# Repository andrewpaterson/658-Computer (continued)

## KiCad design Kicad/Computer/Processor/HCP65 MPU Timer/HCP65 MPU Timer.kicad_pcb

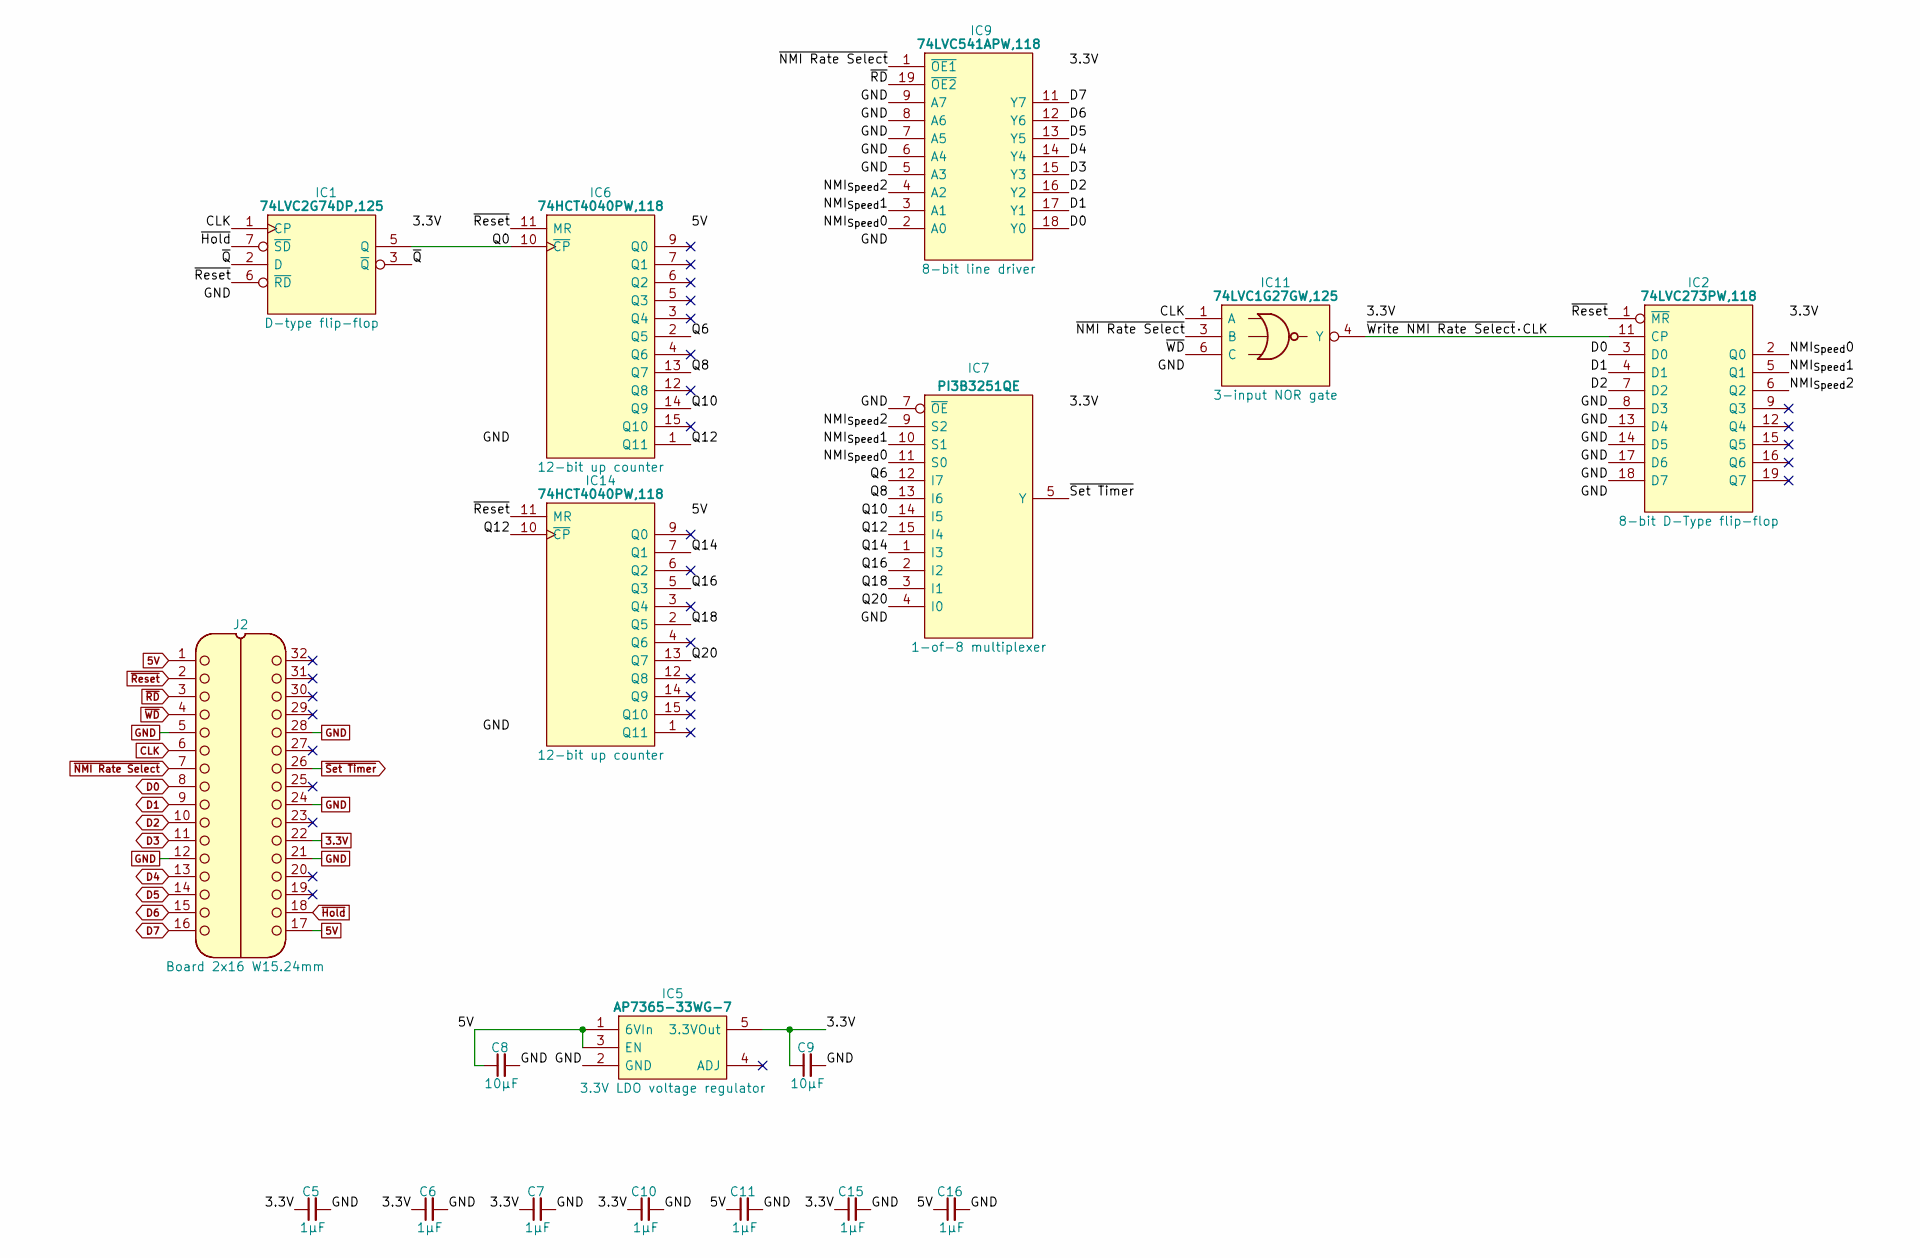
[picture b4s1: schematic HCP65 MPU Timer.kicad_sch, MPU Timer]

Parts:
C5, C6, C7, C10, C11, C15, C16: 1μF; C_0805
C8, C9: 10µF; C_0805
IC1: 74LVC2G74DP,125; SOP65P400X110-8N; Manufacturer_Part_Number 74LVC2G74DP,125; Mouser Part Number 771-74LVC2G74DP-G
IC2: 74LVC273PW,118; SOP65P640X110-20N; Manufacturer_Part_Number 74LVC273PW,118; Mouser Part Number 771-74LVC273PW-T
IC5: AP7365-33WG-7; SOT95P285X130-5N; Manufacturer_Part_Number AP7365-33WG-7; Mouser Part Number 621-AP7365-33WG-7
IC6, IC14: 74HCT4040PW,118; SOP65P640X110-16N; Manufacturer_Part_Number 74HCT4040PW,118; Mouser Part Number 771-HCT4040PW118
IC7: PI3B3251QE; SOP64P599X175-16N; Manufacturer_Part_Number PI3B3251QE; Mouser Part Number 729-PI3B3251QE
IC9: 74LVC541APW,118; SOP65P640X110-20N; Mouser Part Number 771-74LVC541APW-T
IC11: 74LVC1G27GW,125; SOP65P210X110-6N; Mouser Part Number 771-74LVC1G27GW125
J2: Board 2x16 W15.24mm; DIP-32_Board_W15.24mm

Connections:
3.3V: C5.1, C6.1, C7.1, C9.1, C10.1, C15.1, IC1.8 (3V), IC2.20 (3V), IC5.5 (3.3VOut), IC7.16 (3V), IC9.20 (3V), IC11.5 (3V), J2.22
5V: C8.1, C11.1, C16.1, IC5.1 (6VIn), IC5.3 (EN), IC6.16 (5V), IC14.16 (5V), J2.1, J2.17
/NMI_{Speed}0: IC2.2 (Q0), IC7.11 (S0), IC9.2 (A0)
/NMI_{Speed}1: IC2.5 (Q1), IC7.10 (S1), IC9.3 (A1)
/NMI_{Speed}2: IC2.6 (Q2), IC7.9 (S2), IC9.4 (A2)
/Q0: IC1.5 (Q), IC6.10 (~CP)
/Q6: IC6.2 (Q5), IC7.12 (I7)
/Q8: IC6.13 (Q7), IC7.13 (I6)
/Q10: IC6.14 (Q9), IC7.14 (I5)
/Q12: IC6.1 (Q11), IC7.15 (I4), IC14.10 (~CP)
/Q14: IC7.1 (I3), IC14.7 (Q1)
/Q16: IC7.2 (I2), IC14.5 (Q3)
/Q18: IC7.3 (I1), IC14.2 (Q5)
/Q20: IC7.4 (I0), IC14.13 (Q7)
/~Q: IC1.2 (D), IC1.3 (~Q)
/~Write NMI Rate Select·CLK: IC2.11 (CP), IC11.4 (Y)
CLK: IC1.1 (CP), IC11.1 (A), J2.6
D0: IC2.3 (D0), IC9.18 (Y0), J2.8
D1: IC2.4 (D1), IC9.17 (Y1), J2.9
D2: IC2.7 (D2), IC9.16 (Y2), J2.10
D3: IC9.15 (Y3), J2.11
D4: IC9.14 (Y4), J2.13
D5: IC9.13 (Y5), J2.14
D6: IC9.12 (Y6), J2.15
D7: IC9.11 (Y7), J2.16
GND: C5.2, C6.2, C7.2, C8.2, C9.2, C10.2, C11.2, C15.2, C16.2, IC1.4 (GND), IC2.8 (D3), IC2.10 (GND), IC2.13 (D4), IC2.14 (D5), IC2.17 (D6), IC2.18 (D7), IC5.2 (GND), IC6.8 (GND), IC7.7 (~OE), IC7.8 (GND), IC9.5 (A3), IC9.6 (A4), IC9.7 (A5), IC9.8 (A6), IC9.9 (A7), IC9.10 (GND), IC11.2 (GND), IC14.8 (GND), J2.5, J2.12, J2.21, J2.24, J2.28
~Hold: IC1.7 (~SD), J2.18
~NMI Rate Select: IC9.1 (~OE1), IC11.3 (B), J2.7
~RD: IC9.19 (~OE2), J2.3
~Reset: IC1.6 (~RD), IC2.1 (~MR), IC6.11 (MR), IC14.11 (MR), J2.2
~Set Timer: IC7.5 (Y), J2.26
~WD: IC11.6 (C), J2.4

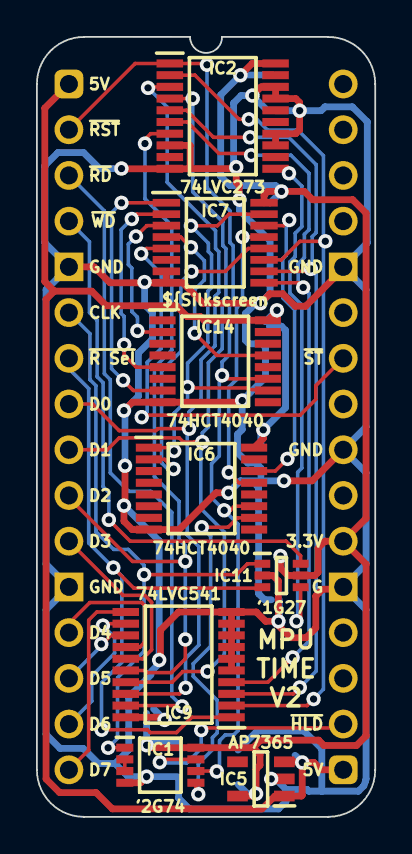
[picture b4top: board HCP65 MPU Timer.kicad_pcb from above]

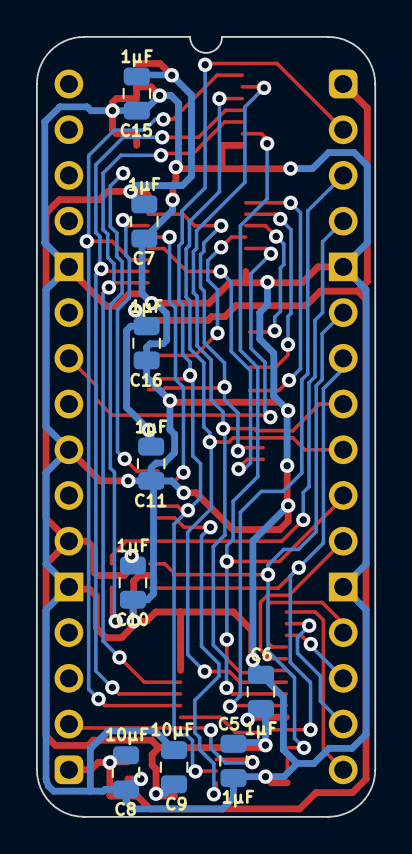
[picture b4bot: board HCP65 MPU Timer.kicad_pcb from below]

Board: 2 copper layers, 18.8 x 43.3 mm, 18 parts (9 on the bottom side), 32 nets.

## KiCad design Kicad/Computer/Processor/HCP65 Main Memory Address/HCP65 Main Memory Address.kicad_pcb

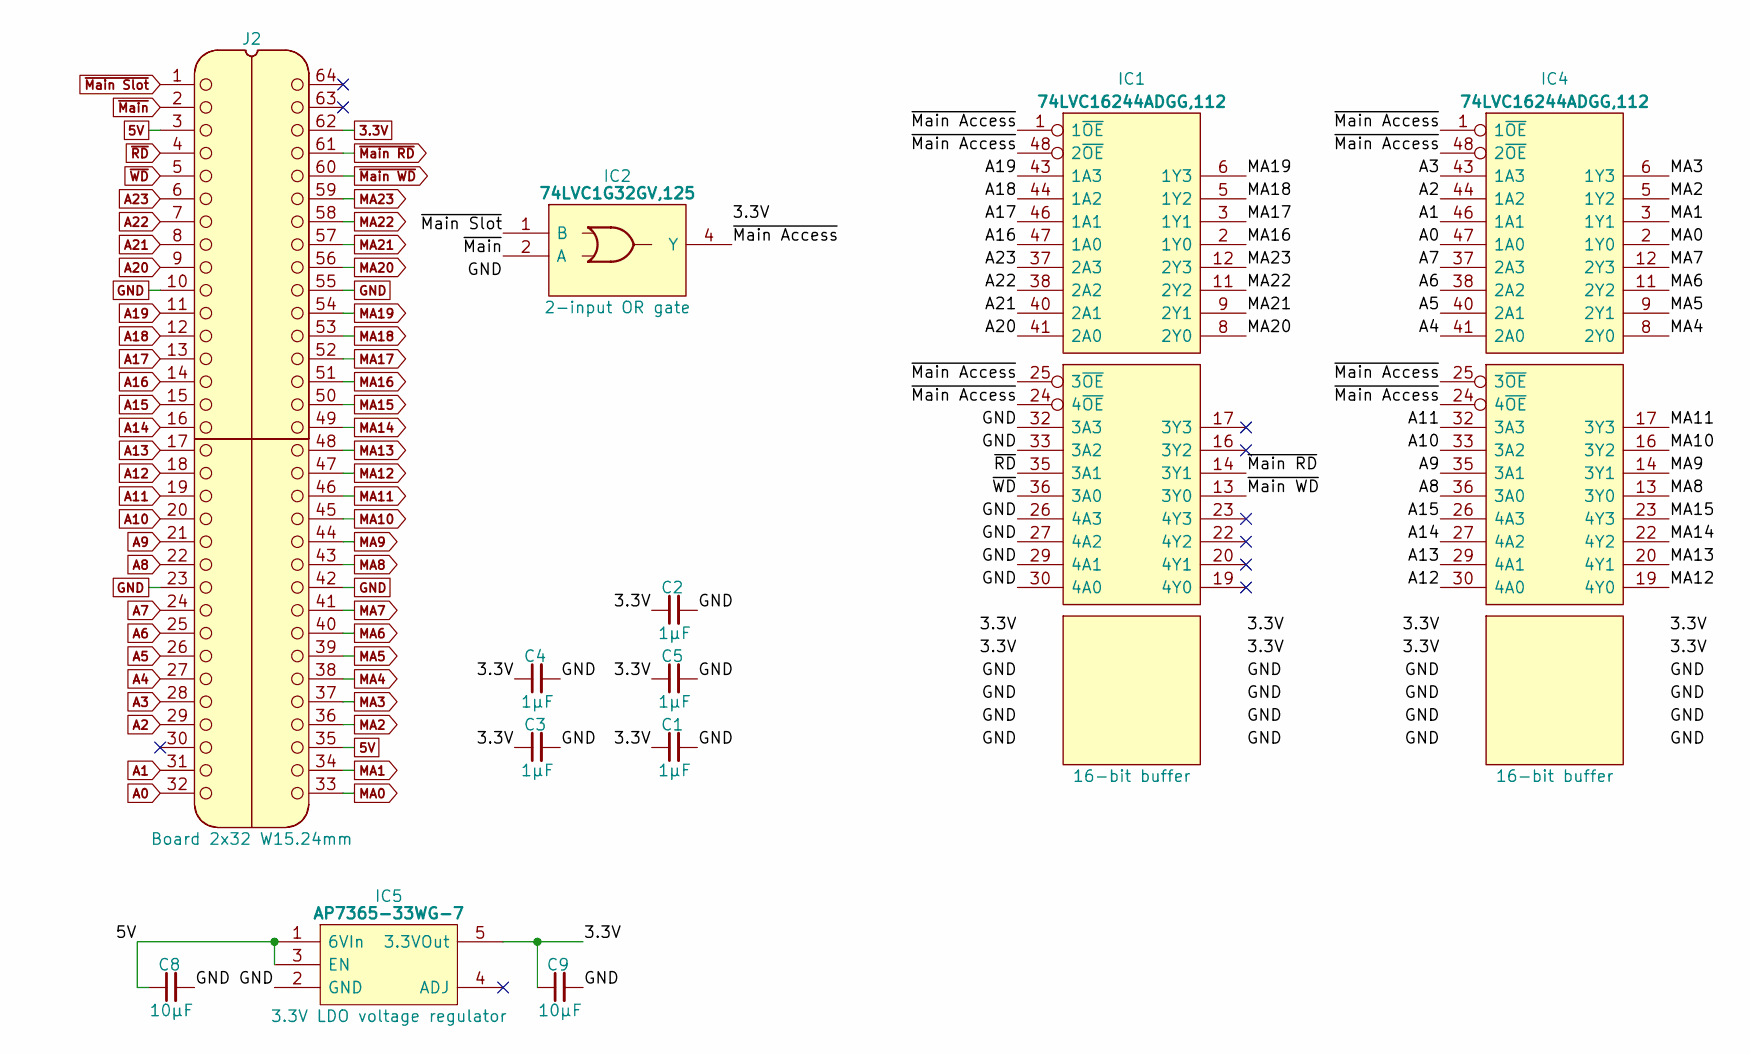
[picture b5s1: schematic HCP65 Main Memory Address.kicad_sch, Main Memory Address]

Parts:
C1, C2, C3, C4, C5: 1μF; C_0805
C8, C9: 10µF; C_0805
IC1, IC4: 74LVC16244ADGG,112; 74LVC16244ADGG112; Manufacturer_Part_Number 74LVC16244ADGG,112; Mouser Part Number 771-74LVC16244DG
IC2: 74LVC1G32GV,125; SOT95P275X110-5N; Manufacturer_Part_Number 74LVC1G32GV,125; Mouser Part Number 771-LVC1G32GV125
IC5: AP7365-33WG-7; SOT95P285X130-5N; Manufacturer_Part_Number AP7365-33WG-7; Mouser Part Number 621-AP7365-33WG-7
J2: Board 2x32 W15.24mm; DIP-64_Board_W15.24mm

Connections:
3.3V: C1.1, C2.1, C3.1, C4.1, C5.1, C9.1, IC1.7 (3V), IC1.18 (3V), IC1.31 (3V), IC1.42 (3V), IC2.5 (3V), IC4.7 (3V), IC4.18 (3V), IC4.31 (3V), IC4.42 (3V), IC5.5 (3.3VOut), J2.62
5V: C8.1, IC5.1 (6VIn), IC5.3 (EN), J2.3, J2.35
/~Main Access: IC1.1 (1~OE), IC1.24 (4~OE), IC1.25 (3~OE), IC1.48 (2~OE), IC2.4 (Y), IC4.1 (1~OE), IC4.24 (4~OE), IC4.25 (3~OE), IC4.48 (2~OE)
A0: IC4.47 (1A0), J2.32
A1: IC4.46 (1A1), J2.31
A2: IC4.44 (1A2), J2.29
A3: IC4.43 (1A3), J2.28
A4: IC4.41 (2A0), J2.27
A5: IC4.40 (2A1), J2.26
A6: IC4.38 (2A2), J2.25
A7: IC4.37 (2A3), J2.24
A8: IC4.36 (3A0), J2.22
A9: IC4.35 (3A1), J2.21
A10: IC4.33 (3A2), J2.20
A11: IC4.32 (3A3), J2.19
A12: IC4.30 (4A0), J2.18
A13: IC4.29 (4A1), J2.17
A14: IC4.27 (4A2), J2.16
A15: IC4.26 (4A3), J2.15
A16: IC1.47 (1A0), J2.14
A17: IC1.46 (1A1), J2.13
A18: IC1.44 (1A2), J2.12
A19: IC1.43 (1A3), J2.11
A20: IC1.41 (2A0), J2.9
A21: IC1.40 (2A1), J2.8
A22: IC1.38 (2A2), J2.7
A23: IC1.37 (2A3), J2.6
GND: C1.2, C2.2, C3.2, C4.2, C5.2, C8.2, C9.2, IC1.4 (GND), IC1.10 (GND), IC1.15 (GND), IC1.21 (GND), IC1.26 (4A3), IC1.27 (4A2), IC1.28 (GND), IC1.29 (4A1), IC1.30 (4A0), IC1.32 (3A3), IC1.33 (3A2), IC1.34 (GND), IC1.39 (GND), IC1.45 (GND), IC2.3 (GND), IC4.4 (GND), IC4.10 (GND), IC4.15 (GND), IC4.21 (GND), IC4.28 (GND), IC4.34 (GND), IC4.39 (GND), IC4.45 (GND), IC5.2 (GND), J2.10, J2.23, J2.42, J2.55
MA0: IC4.2 (1Y0), J2.33
MA1: IC4.3 (1Y1), J2.34
MA2: IC4.5 (1Y2), J2.36
MA3: IC4.6 (1Y3), J2.37
MA4: IC4.8 (2Y0), J2.38
MA5: IC4.9 (2Y1), J2.39
MA6: IC4.11 (2Y2), J2.40
MA7: IC4.12 (2Y3), J2.41
MA8: IC4.13 (3Y0), J2.43
MA9: IC4.14 (3Y1), J2.44
MA10: IC4.16 (3Y2), J2.45
MA11: IC4.17 (3Y3), J2.46
MA12: IC4.19 (4Y0), J2.47
MA13: IC4.20 (4Y1), J2.48
MA14: IC4.22 (4Y2), J2.49
MA15: IC4.23 (4Y3), J2.50
MA16: IC1.2 (1Y0), J2.51
MA17: IC1.3 (1Y1), J2.52
MA18: IC1.5 (1Y2), J2.53
MA19: IC1.6 (1Y3), J2.54
MA20: IC1.8 (2Y0), J2.56
MA21: IC1.9 (2Y1), J2.57
MA22: IC1.11 (2Y2), J2.58
MA23: IC1.12 (2Y3), J2.59
~Main RD: IC1.14 (3Y1), J2.61
~Main Slot: IC2.1 (B), J2.1
~Main WD: IC1.13 (3Y0), J2.60
~Main: IC2.2 (A), J2.2
~RD: IC1.35 (3A1), J2.4
~WD: IC1.36 (3A0), J2.5

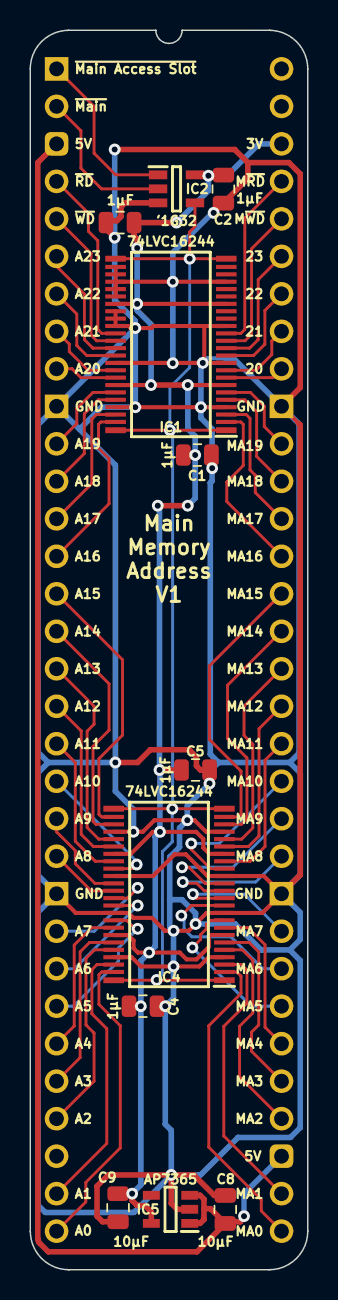
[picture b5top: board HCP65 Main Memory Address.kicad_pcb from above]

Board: 2 copper layers, 18.8 x 84.0 mm, 12 parts (0 on the bottom side), 58 nets.

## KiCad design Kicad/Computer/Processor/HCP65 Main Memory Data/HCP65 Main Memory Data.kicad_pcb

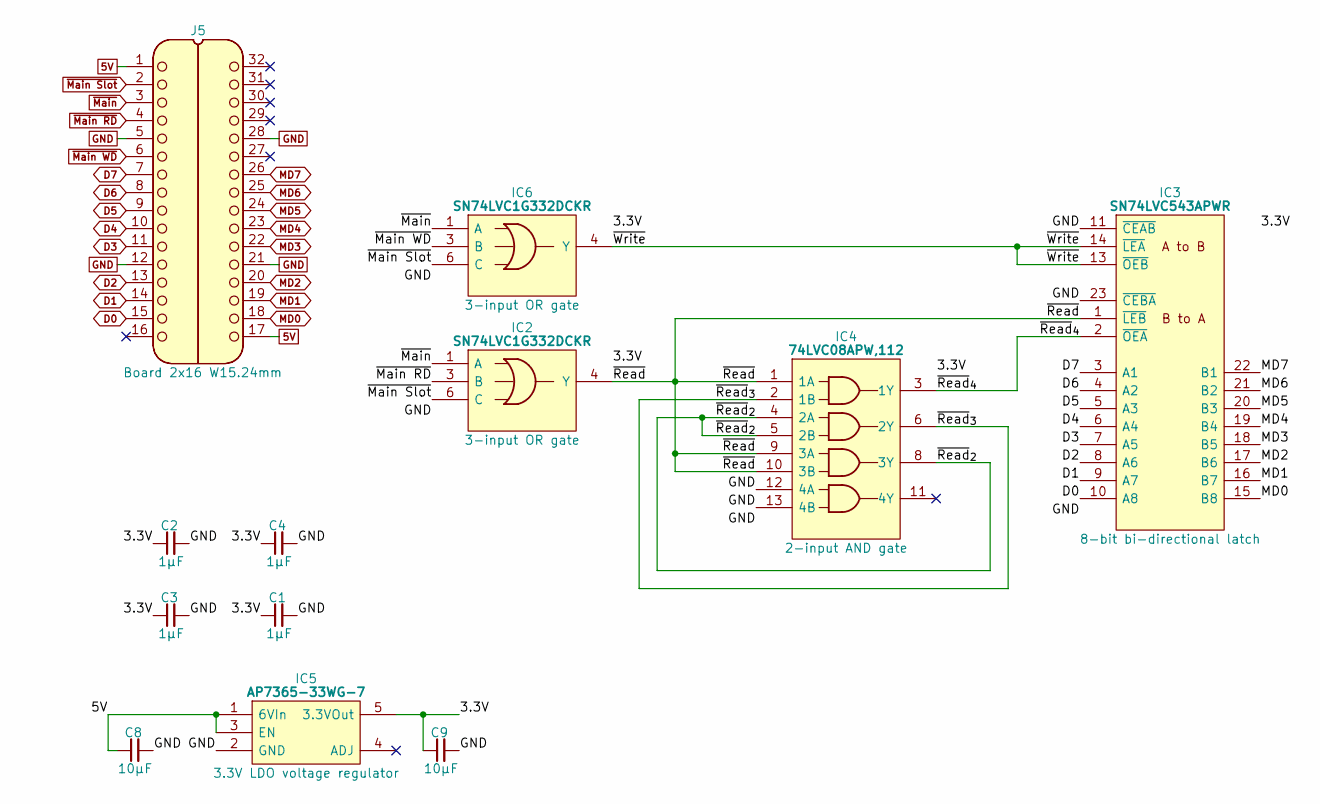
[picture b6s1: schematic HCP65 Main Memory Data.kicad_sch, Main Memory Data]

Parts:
C1, C2, C3, C4: 1μF; C_0805
C8, C9: 10µF; C_0805
IC2, IC6: SN74LVC1G332DCKR; SOT65P210X110-6N; Mouser Part Number 595-SN74LVC1G332DCKR
IC3: SN74LVC543APWR; SOP65P640X120-24N; Mouser Part Number 595-SN74LVC543APWR
IC4: 74LVC08APW,112; SOP65P640X110-14N; Manufacturer_Part_Number 74LVC08APW,112; Mouser Part Number 771-74LVC08APW
IC5: AP7365-33WG-7; SOT95P285X130-5N; Manufacturer_Part_Number AP7365-33WG-7; Mouser Part Number 621-AP7365-33WG-7
J5: Board 2x16 W15.24mm; DIP-32_Board_W15.24mm

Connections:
5V: C8.1, IC5.1 (6VIn), IC5.3 (EN), J5.1, J5.17
/3.3V: C1.1, C2.1, C3.1, C4.1, C9.1, IC2.5 (3V), IC3.24 (3V), IC4.14 (3V), IC5.5 (3.3VOut), IC6.5 (3V)
/~Read: IC2.4 (Y), IC3.1 (~LEB), IC4.1 (1A), IC4.9 (3A), IC4.10 (3B)
/~Read_{2}: IC4.4 (2A), IC4.5 (2B), IC4.8 (3Y)
/~Read_{3}: IC4.2 (1B), IC4.6 (2Y)
/~Read_{4}: IC3.2 (~OEA), IC4.3 (1Y)
/~Write: IC3.13 (~OEB), IC3.14 (~LEA), IC6.4 (Y)
D0: IC3.10 (A8), J5.15
D1: IC3.9 (A7), J5.14
D2: IC3.8 (A6), J5.13
D3: IC3.7 (A5), J5.11
D4: IC3.6 (A4), J5.10
D5: IC3.5 (A3), J5.9
D6: IC3.4 (A2), J5.8
D7: IC3.3 (A1), J5.7
GND: C1.2, C2.2, C3.2, C4.2, C8.2, C9.2, IC2.2 (GND), IC3.11 (~CEAB), IC3.12 (GND), IC3.23 (~CEBA), IC4.7 (GND), IC4.12 (4A), IC4.13 (4B), IC5.2 (GND), IC6.2 (GND), J5.5, J5.12, J5.21, J5.28
MD0: IC3.15 (B8), J5.18
MD1: IC3.16 (B7), J5.19
MD2: IC3.17 (B6), J5.20
MD3: IC3.18 (B5), J5.22
MD4: IC3.19 (B4), J5.23
MD5: IC3.20 (B3), J5.24
MD6: IC3.21 (B2), J5.25
MD7: IC3.22 (B1), J5.26
~Main RD: IC2.3 (B), J5.4
~Main Slot: IC2.6 (C), IC6.6 (C), J5.2
~Main WD: IC6.3 (B), J5.6
~Main: IC2.1 (A), IC6.1 (A), J5.3

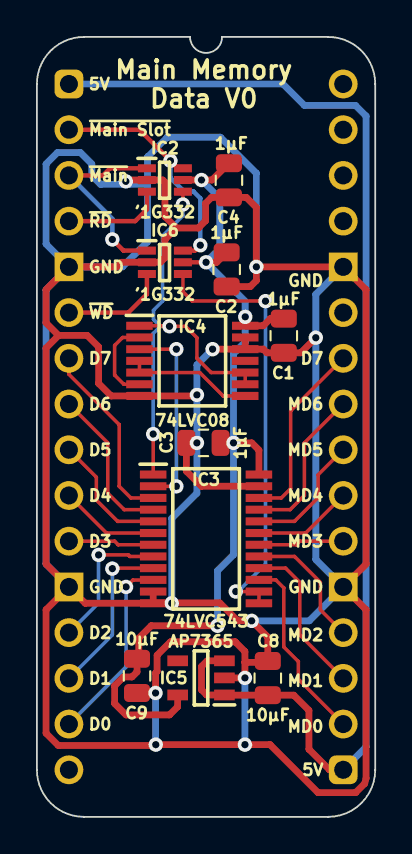
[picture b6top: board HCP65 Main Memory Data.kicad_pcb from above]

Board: 2 copper layers, 18.8 x 43.3 mm, 12 parts (0 on the bottom side), 28 nets.

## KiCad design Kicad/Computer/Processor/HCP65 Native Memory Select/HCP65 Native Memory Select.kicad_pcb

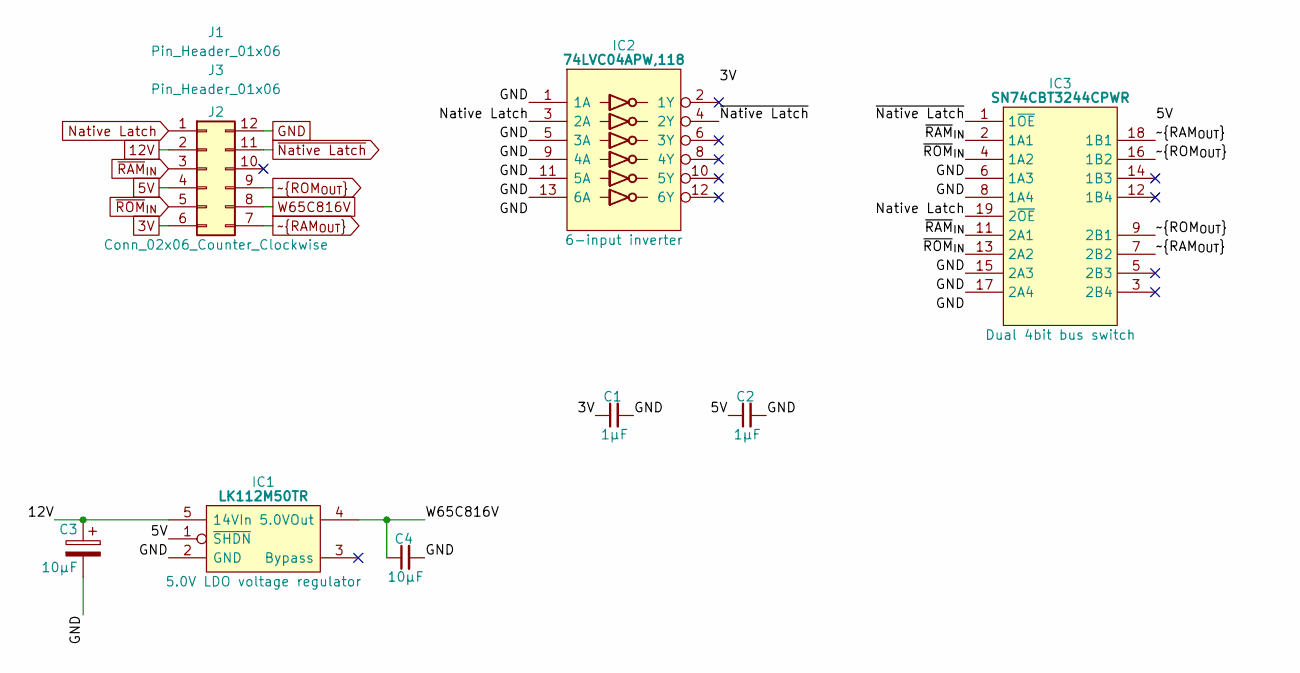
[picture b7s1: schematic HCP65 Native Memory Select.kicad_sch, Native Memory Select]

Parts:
C1, C2: 1μF; C_0805
C3: 10μF; CP_Radial_D4.0mm_P2.00mm
C4: 10µF; C_0805
IC1: LK112M50TR; SOT95P285X130-5N; Manufacturer_Part_Number LK112M50TR
IC2: 74LVC04APW,118; SOP65P640X110-14N; Mouser Part Number 771-74LVC04APW-T
IC3: SN74CBT3244CPWR; SOP65P640X120-20N; Manufacturer_Part_Number SN74CBT3244CPWR; Mouser Part Number 595-SN74CBT3244CPWR
J1, J3: Pin_Header_01x06; PinHeader_1x06_P2.54mm_Vertical
J2: Conn_02x06_Counter_Clockwise; DIP-12_Board_W22.86mm_Alt

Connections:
3V: C1.1, IC2.14 (3V), J2.6
5V: C2.1, IC1.1 (~SHDN), IC3.20 (5V), J2.4
12V: C3.1, IC1.5 (14VIn), J2.2
GND: C1.2, C2.2, C3.2, C4.2, IC1.2 (GND), IC2.1 (1A), IC2.5 (3A), IC2.7 (GND), IC2.9 (4A), IC2.11 (5A), IC2.13 (6A), IC3.6 (1A3), IC3.8 (1A4), IC3.10 (GND), IC3.15 (2A3), IC3.17 (2A4), J2.12
Native Latch: IC2.3 (2A), IC3.19 (2~OE), J2.1
W65C816V: C4.1, IC1.4 (5.0VOut), J2.8
~Native Latch: IC2.4 (2Y), IC3.1 (1~OE), J2.11
~RAM_{OUT}: IC3.7 (2B2), IC3.18 (1B1), J2.7
~RAM_{IN}: IC3.2 (1A1), IC3.11 (2A1), J2.3
~ROM_{OUT}: IC3.9 (2B1), IC3.16 (1B2), J2.9
~ROM_{IN}: IC3.4 (1A2), IC3.13 (2A2), J2.5

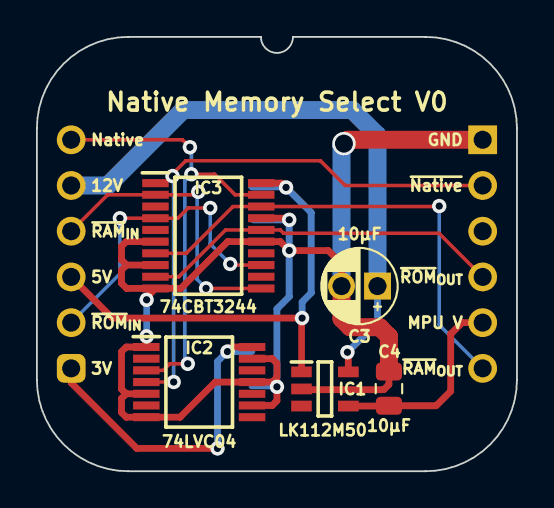
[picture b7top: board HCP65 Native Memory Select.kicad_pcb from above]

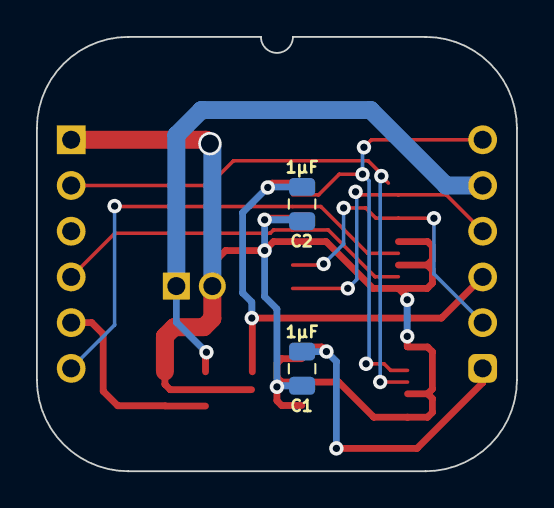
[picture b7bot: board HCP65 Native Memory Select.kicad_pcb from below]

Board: 2 copper layers, 26.7 x 24.1 mm, 10 parts (4 on the bottom side), 11 nets.
